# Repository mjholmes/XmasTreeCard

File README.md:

# XmasTreeCard
#### A geeky Christmas card with LEDs and an OLED display

This circuit and board assembled into a Christmas tree shaped card with 11 LEDs driven by a 12-bit shift register and a small, 0.91", OLED display.

It's a bit rough and needs some more polish when time allows.

This work is licensed under a [Creative Commons Attribution-ShareAlike 4.0 International License](http://creativecommons.org/licenses/by-sa/4.0/).

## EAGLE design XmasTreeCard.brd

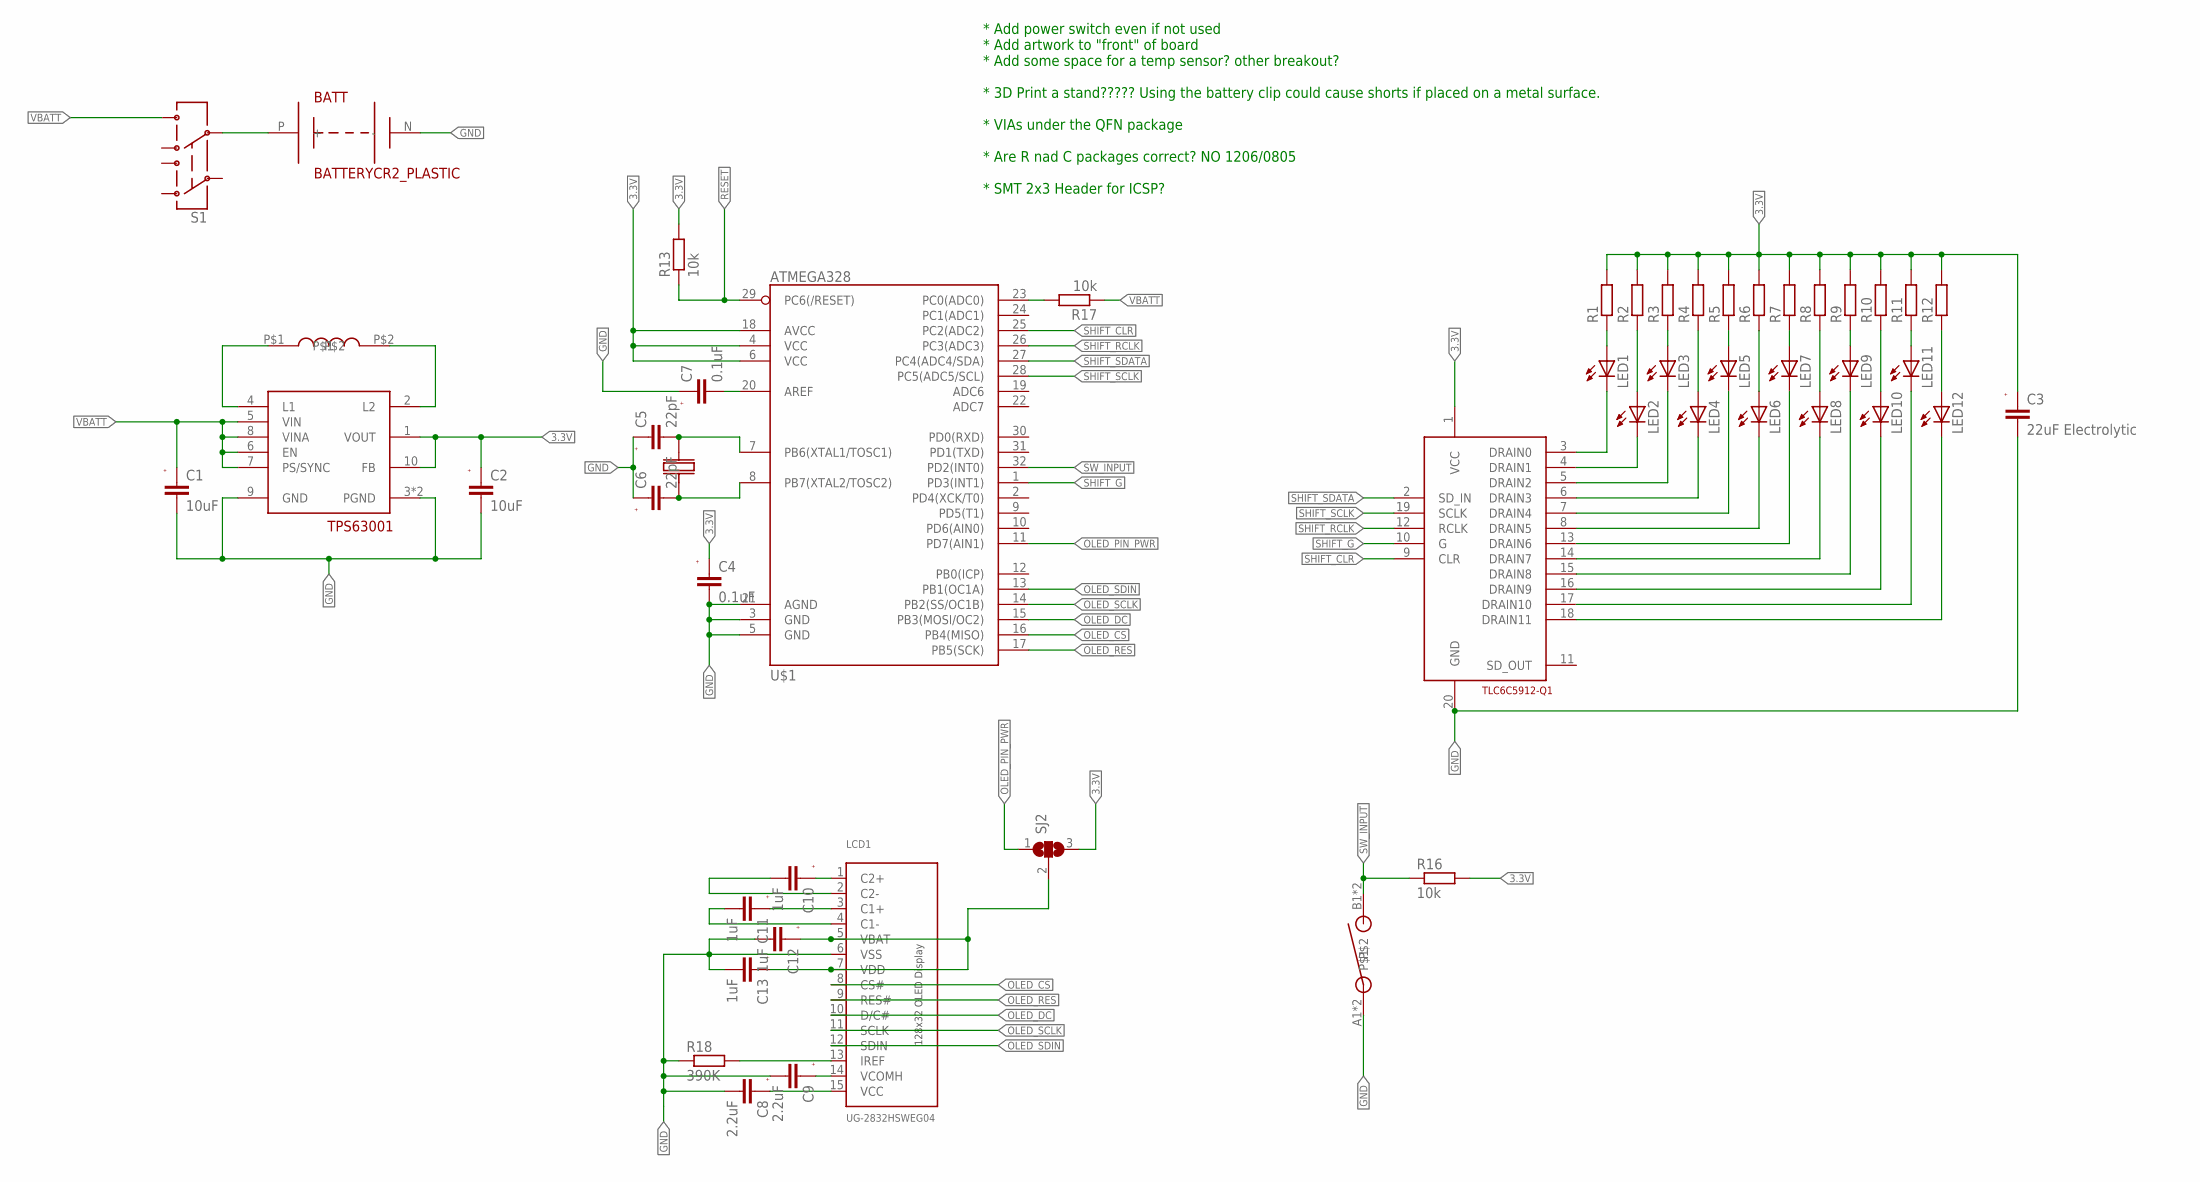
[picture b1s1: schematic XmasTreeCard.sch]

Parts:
BATT: BATTERYCR2_PLASTIC; BATT_SMD_CR2_PLASTIC
C1, C2: 10uF; C1206
C3: 22uF Electrolytic; CAP_2012-15
C4, C7: 0.1uF; C0805K
C5, C6: 22pF; C0805K
C8, C9: 2.2uF; C1206
C10, C11, C12, C13: 1uF; C1206
LCD1: UG-2832HSWEG04; UG-283HSWEG04_FOLDAROUND
LED1, LED2, LED3, LED4, LED5, LED6, LED7, LED8, LED9, LED10, LED11, LED12: LEDCHIPLED_0805; CHIPLED_0805
R1, R2, R3, R4, R5, R6, R7, R8, R9, R10, R11, R12: R-EUR0805; R0805
R13, R16, R17: 10k; R0805
R18: 390K; R0805
S1: SWITCH-DPDTMMS228; MMS_228_T
SJ2: SJ2W; SJ_2
SW1: SWITCH_SPST6X6TACTILE; SWITCH_SPST_6X6_TACTILE
U$1: ATMEGA328; TQFP32-08
U$2: COILCRAFT_LPS4012
U$3: TPS63001DRC; QFN10_3X3MM
U$4: TLC6C5912-Q1; TSSOP-20
U$5: CRYSTAL_ABM03; ABM_CRYSTAL

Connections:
3.3V: C2.1, C3.P (1), C4.1, R1.2, R2.2, R3.2, R4.2, R5.2, R6.2, R7.2, R8.2, R9.2, R10.2, R11.2, R12.2, R13.2, R16.2, SJ2.3, U$1.4 (VCC), U$1.6 (VCC), U$1.18 (AVCC), U$3.1 (VOUT), U$3.10 (FB), U$4.1 (VCC)
GND: BATT.N (-), C1.2, C2.2, C3.N (2), C4.2, C5.1, C6.1, C7.1, C8.2, C9.2, C12.2, C13.2, LCD1.6 (VSS), R18.1, SW1.A1, SW1.A2, U$1.3 (GND), U$1.5 (GND), U$1.21 (AGND), U$3.3 (PGND), U$3.9 (GND), U$3.11 (PGND), U$4.20 (GND)
unnamed: U$2.P$1, U$3.4 (L1)
unnamed: U$2.P$2, U$3.2 (L2)
unnamed: LED1.A, R1.1
unnamed: LED2.A, R2.1
unnamed: LED3.A, R3.1
unnamed: LED4.A, R4.1
unnamed: LED5.A, R5.1
unnamed: LED6.A, R6.1
unnamed: LED7.A, R7.1
unnamed: LED8.A, R8.1
unnamed: LED9.A, R9.1
unnamed: LED10.A, R10.1
unnamed: LED11.A, R11.1
unnamed: LED12.A, R12.1
unnamed: LED1.C, U$4.3 (DRAIN0)
unnamed: LED2.C, U$4.4 (DRAIN1)
unnamed: LED3.C, U$4.5 (DRAIN2)
unnamed: LED4.C, U$4.6 (DRAIN3)
unnamed: LED5.C, U$4.7 (DRAIN4)
unnamed: LED6.C, U$4.8 (DRAIN5)
unnamed: LED7.C, U$4.13 (DRAIN6)
unnamed: LED8.C, U$4.14 (DRAIN7)
unnamed: LED9.C, U$4.15 (DRAIN8)
unnamed: LED10.C, U$4.16 (DRAIN9)
unnamed: LED11.C, U$4.17 (DRAIN10)
unnamed: LED12.C, U$4.18 (DRAIN11)
unnamed: C5.2, U$1.7 (PB6(XTAL1/TOSC1)), U$5.2
unnamed: BATT.P (+), S1.6 (5)
unnamed: C6.2, U$1.8 (PB7(XTAL2/TOSC2)), U$5.1
unnamed: C7.2, U$1.20 (AREF)
unnamed: R17.2, U$1.23 (PC0(ADC0))
unnamed: C10.2, LCD1.2 (C2-)
unnamed: C10.1, LCD1.1 (C2+)
unnamed: C11.2, LCD1.4 (C1-)
unnamed: C11.1, LCD1.3 (C1+)
unnamed: LCD1.13 (IREF), R18.2
unnamed: C9.1, LCD1.14 (VCOMH)
unnamed: C8.1, LCD1.15 (VCC)
unnamed: C12.1, C13.1, LCD1.5 (VBAT), LCD1.7 (VDD), SJ2.2
OLED_CS: LCD1.8 (CS#), U$1.16 (PB4(MISO))
OLED_DC: LCD1.10 (D/C#), U$1.15 (PB3(MOSI/OC2))
OLED_PIN_PWR: SJ2.1, U$1.11 (PD7(AIN1))
OLED_RES: LCD1.9 (RES#), U$1.17 (PB5(SCK))
OLED_SCLK: LCD1.11 (SCLK), U$1.14 (PB2(SS/OC1B))
OLED_SDIN: LCD1.12 (SDIN), U$1.13 (PB1(OC1A))
RESET: R13.1, U$1.29 (PC6(/RESET))
SHIFT_CLR: U$1.25 (PC2(ADC2)), U$4.9 (CLR)
SHIFT_G: U$1.1 (PD3(INT1)), U$4.10 (G)
SHIFT_RCLK: U$1.26 (PC3(ADC3)), U$4.12 (RCLK)
SHIFT_SCLK: U$1.28 (PC5(ADC5/SCL)), U$4.19 (SCLK)
SHIFT_SDATA: U$1.27 (PC4(ADC4/SDA)), U$4.2 (SD_IN)
SW_INPUT: R16.1, SW1.B1, SW1.B2, U$1.32 (PD2(INT0))
VBATT: C1.1, R17.1, S1.7 (6), U$3.5 (VIN), U$3.6 (EN), U$3.7 (PS/SYNC), U$3.8 (VINA)

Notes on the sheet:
* Add power switch even if not used * Add artwork to "front" of board * Add some space for a temp sensor? other breakout? * 3D Print a stand????? Using the battery clip could cause shorts if placed on a metal surface. * VIAs under the QFN package * Are R nad C packages correct? NO 1206/0805 * SMT 2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

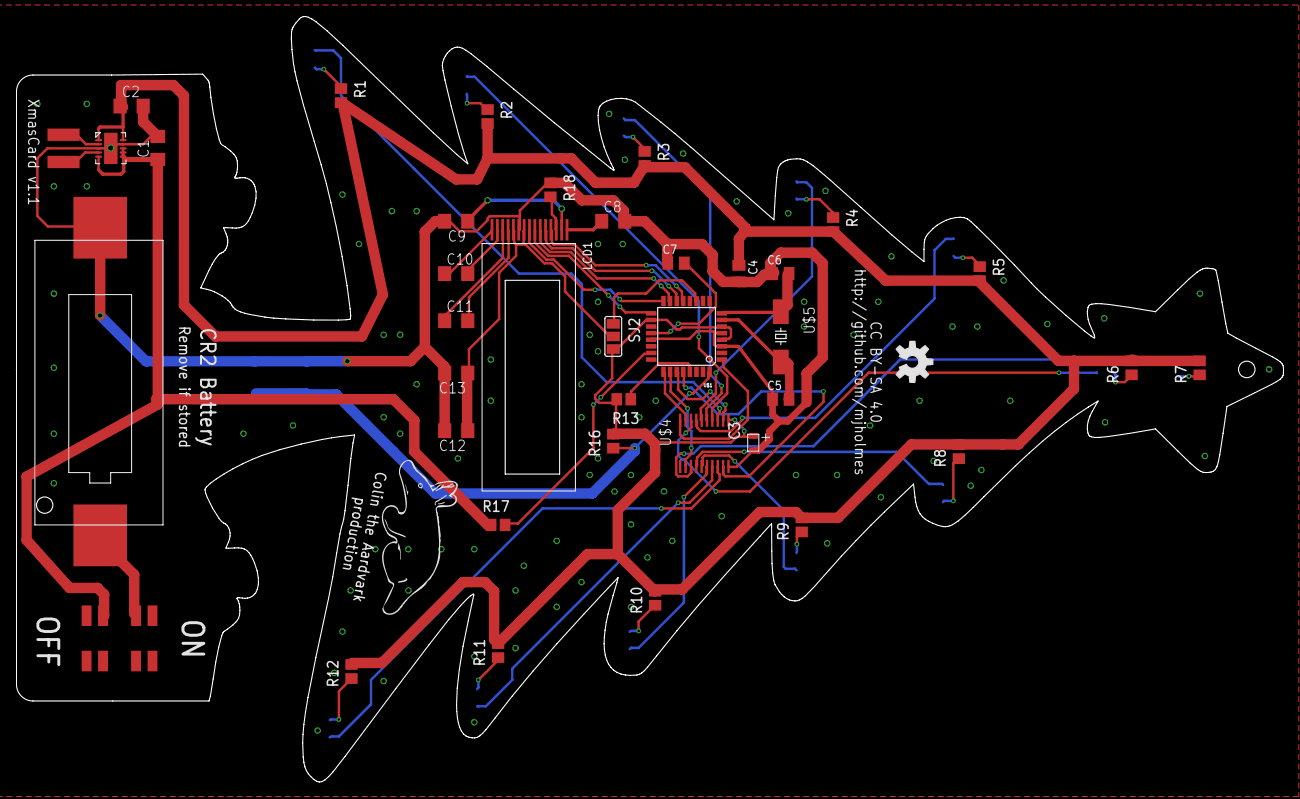
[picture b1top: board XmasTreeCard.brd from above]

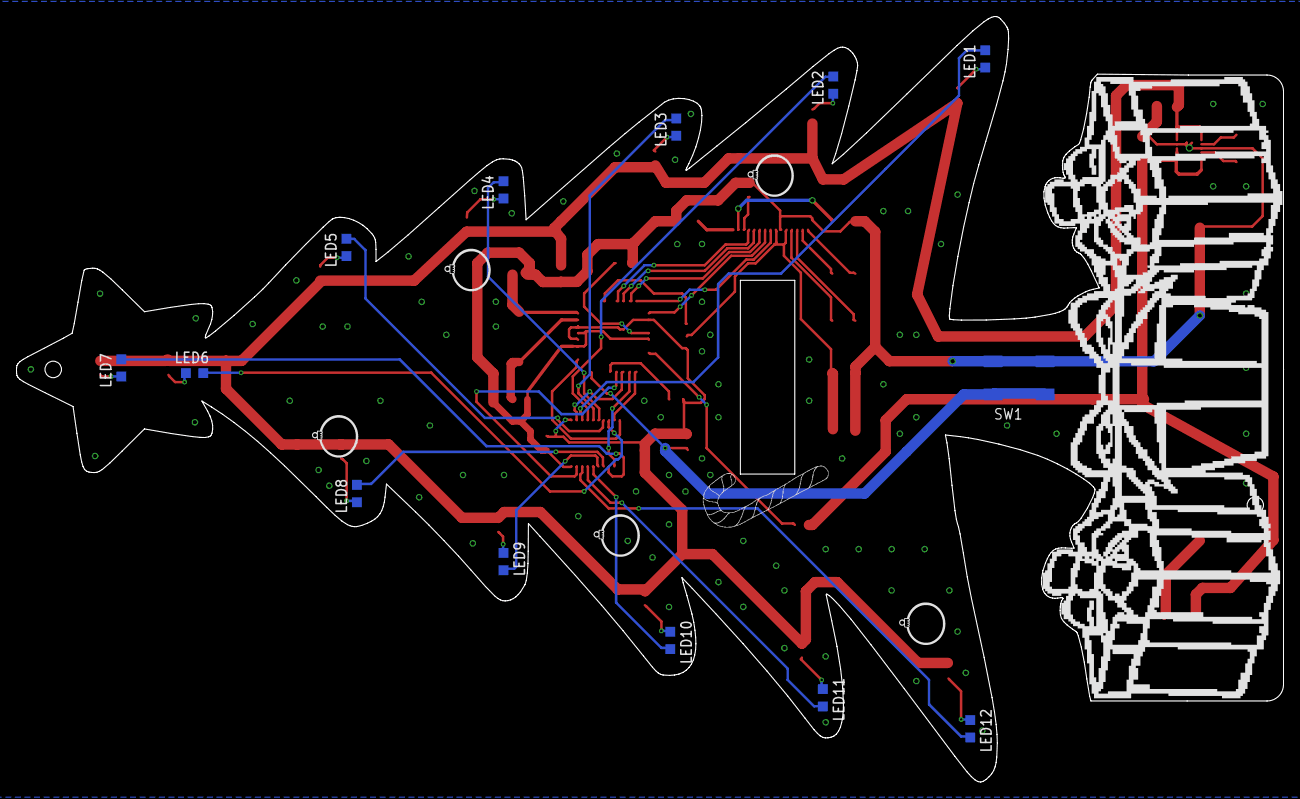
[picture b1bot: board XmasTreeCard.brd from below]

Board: 2 copper layers, 153.7 x 92.9 mm, 52 parts (13 on the bottom side), 55 nets.

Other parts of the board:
U$6: OSHW-LOGO-M

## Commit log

2014-11-26 :lollipop: Added .gitattributes
2014-12-03 Added CC BY-SA 4.0 License
2014-12-03 Added v1 gerbers
    The v1 Gerbers were created before the CC BY-SA 4.0 license details were
    added but can be used under that license.

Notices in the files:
parts and their libraries:
SparkFun-Aesthetics: Licensing: CC v3.0 Share-Alike You are welcome to use this library for commercial purposes.
